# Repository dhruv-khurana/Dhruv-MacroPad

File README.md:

# My adaptation of the HackPad!

This is my adaptation of the blueprint hackpad by hackclub. I spent around 10 Hours on it, and used KiCad and Fusion360 for it's design

**Features**
- 9 Cherry MX Mechanical Switches in a 3x3 Arrangement 
- Rotary Encoder
- 0.96" OLED Display

  **PCB**

**CAD Model**

The case has a Lip where the PCB can snap in:

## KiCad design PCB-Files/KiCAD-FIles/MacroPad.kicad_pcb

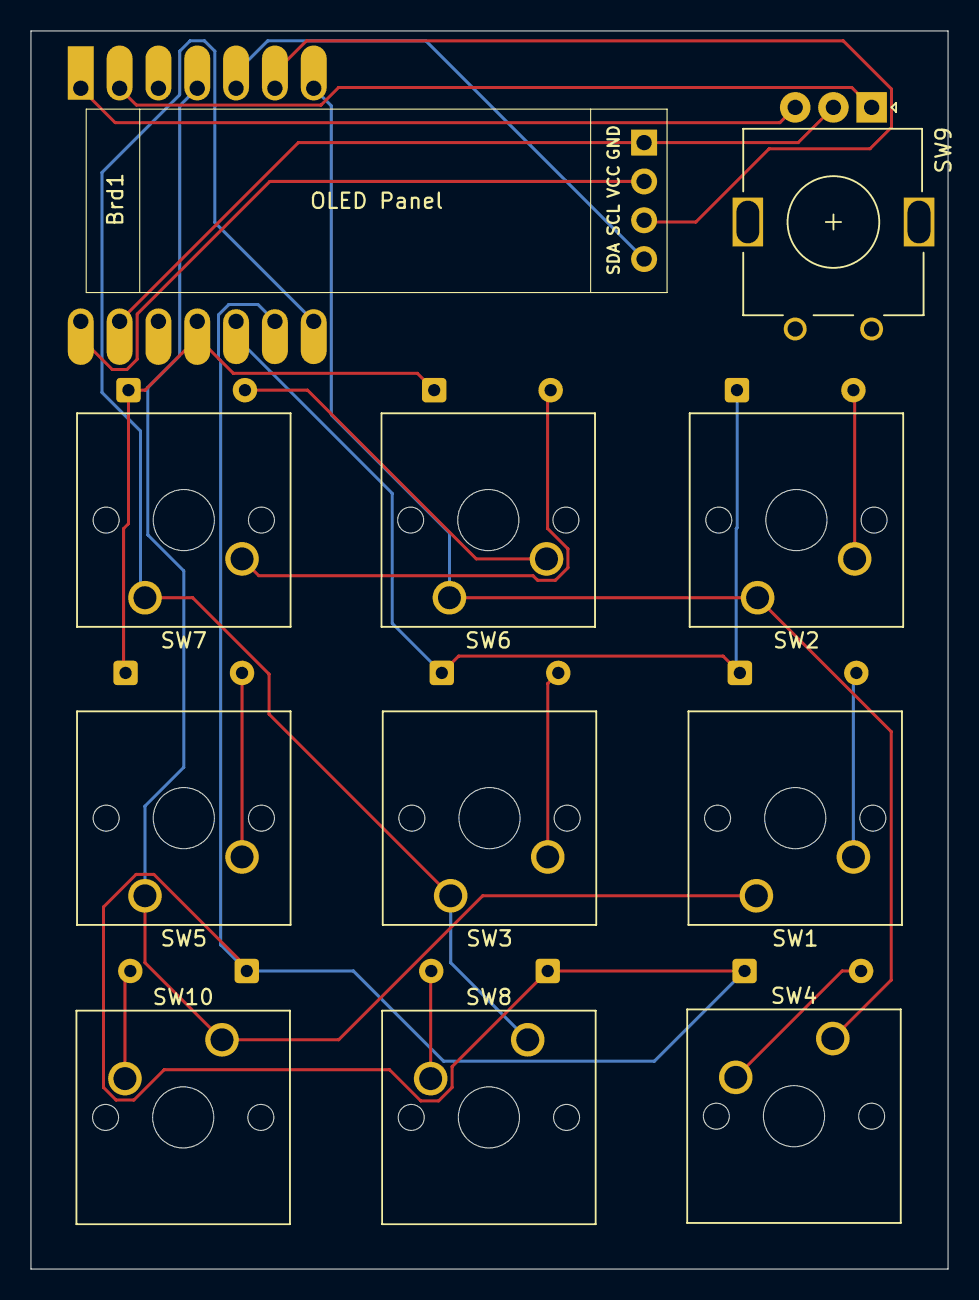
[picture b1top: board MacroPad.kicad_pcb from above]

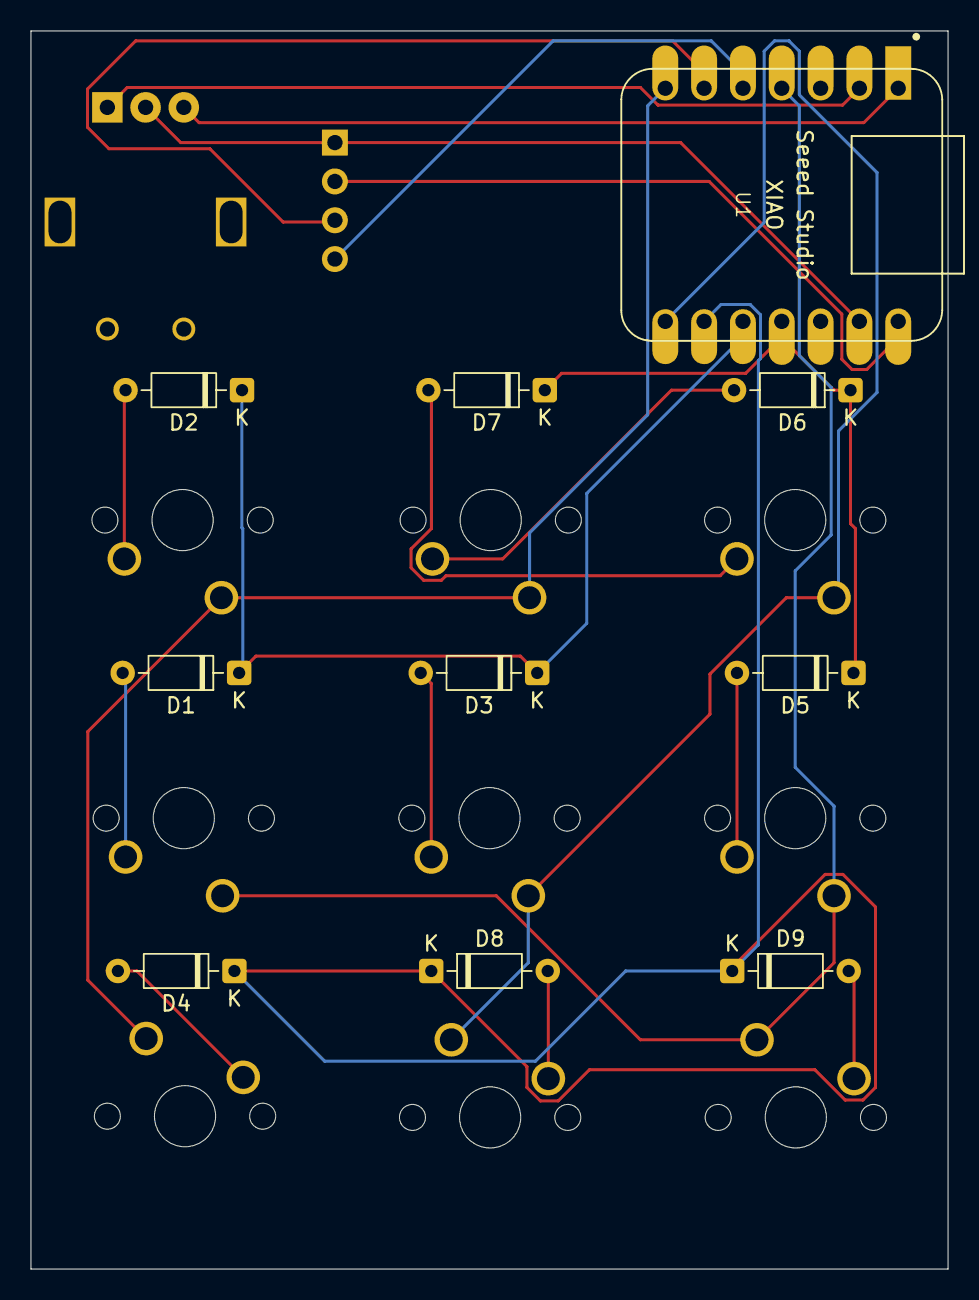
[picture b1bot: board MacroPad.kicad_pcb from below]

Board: 2 copper layers, 60.0 x 81.0 mm, 21 parts (10 on the bottom side), 21 nets.

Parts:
Brd1: SSD1306; SSD1306-0.91-OLED-4pin-128x32
D1, D2, D3, D4, D5, D6, D7, D8, D9: 1N914; D_DO-35_SOD27_P7.62mm_Horizontal
SW1, SW2, SW3, SW4, SW5, SW6, SW7, SW8, SW10: SW_Push; SW_Cherry_MX_1.00u_PCB
SW9: RotaryEncoder_Switch; RotaryEncoder_Alps_EC11E_Vertical_H20mm
U1: MOUDLE-SEEEDUINO-XIAO; XIAO-Generic-Hybrid-14P-2.54-21X17.8MM

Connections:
GND: Brd1.1 (GND), SW9.C, U1.13 (GND)
unnamed: Brd1.3 (SCL), U1.6 (PA9_A5_D5_SCL)
unnamed: Brd1.4 (SDA), U1.5 (PA8_A4_D4_SDA)
unnamed: D1.2 (A), SW1.2
unnamed: D1.1 (K), D2.1 (K), D3.1 (K), U1.10 (PA5_A9_D9_MISO)
unnamed: D2.2 (A), SW2.2
unnamed: D3.2 (A), SW3.2
unnamed: D4.2 (A), SW4.2
unnamed: D4.1 (K), D8.1 (K), D9.1 (K), U1.9 (PA7_A8_D8_SCK)
unnamed: D5.2 (A), SW5.2
unnamed: D5.1 (K), D6.1 (K), D7.1 (K), U1.11 (PA6_A10_D10_MOSI)
unnamed: D6.2 (A), SW6.2
unnamed: D7.2 (A), SW7.2
unnamed: D8.2 (A), SW8.2
unnamed: D9.2 (A), SW10.2
unnamed: SW9.B, U1.1 (PA02_A0_D0)
unnamed: SW9.A, U1.2 (PA4_A1_D1)
unnamed: SW1.1, SW5.1, SW10.1, U1.4 (PA11_A3_D3)
unnamed: SW2.1, SW4.1, SW6.1, U1.7 (PB08_A6_D6_TX)
unnamed: SW3.1, SW7.1, SW8.1, U1.8 (PB09_A7_D7_RX)
VCC: Brd1.2 (VCC), U1.14 (5V)

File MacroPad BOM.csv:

"Id";"Designator";"Footprint";"Quantity";"Designation";"Supplier and ref";
1;"SW6,SW3,SW1,SW7,SW2,SW10,SW8,SW4,SW5";"SW_Cherry_MX_1.00u_PCB";9;"SW_Push";;;
2;"SW9";"RotaryEncoder_Alps_EC11E_Vertical_H20mm";1;"RotaryEncoder_Switch";;;
3;"Brd1";"SSD1306-0.91-OLED-4pin-128x32";1;"SSD1306";;;
4;"D7,D3,D8,D9,D5,D4,D1,D2,D6";"D_DO-35_SOD27_P7.62mm_Horizontal";9;"1N914";;;
5;"U1";"XIAO-Generic-Hybrid-14P-2.54-21X17.8MM";1;"MOUDLE-SEEEDUINO-XIAO";;;

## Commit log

2026-02-17 Fix header formatting in README.md
2026-02-17 Initialize KMK keyboard with OLED and encoder support
2026-02-17 Add renders.txt with initial content
2026-02-17 Add initial content to cad.txt
2026-02-17 Add initial KiCAD project file description
2026-02-17 Add Gerber.txt to document file location
2026-02-17 Add other.txt with placeholder text
2026-02-17 Enhance README with image and features section
    Added an image and features list to the README.
2026-02-17 Rename MacroPad Render 2.png to Render2.png
2026-02-17 Rename MacroPad Render 3.png to Render3.png
2026-02-17 Revise README with new images and project details
    Updated images and added project details including features and CAD model information.
2026-02-17 Update images in README.md for macropad
2026-02-17 Correct time spent on HackPad adaptation
    Updated the time spent on the project from 12 to 10 hours.
